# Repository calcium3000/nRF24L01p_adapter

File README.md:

# nRF24L01+ to Raspberry Pi adapter
Here lies a simple adapter for attaching one of those dirt-cheap nRF24L01+ modules to a Raspberry Pi (all models).  As seen on calcium3000.wordpress.com.

## Assembly
Pads are included for an optional 0805 surface mount capacitor, C1.  Some have reported that such a capacitor helps prevent wonkiness when transmitting at higher output (0dBm).  If extra capacitance at the power rails sounds peachy, install this guy first to make life easier later on.

Next, install P1 with a 2x4, 0.1" (2.54mm) female header such that the header sticks out of the side labeled *BOTTOM* -- this is also where the P1 designator sits.  P2 can either be another 2x4 female header for easy exchange of nRFs, or an nRF module can be soldered directly in.  Either way, make sure the header/radio protrudes from the opposite side of P1, labeled *TOP*.  If the nRF is directly soldered in, don't forget to clip the leads on the bottom side lest they sit dangerously close to the Broadcom chip and look quite ugly.

## Connection to RPi
This adapter is meant to plug directly into the GPIO header of a Raspberry Pi, facing inwards towards the processor.  Our adapter friend sits directly in the middle of the header on pins 17 to 24 (+3.3V to BCM 8) leaving 8 rows (16 pins) on each side when seated correctly.  See https://pinout.xyz for a good pin diagram.

Below is a table describing the pin functions and how they map from the RPi to the nRF24L01+.

| Pin function | nRF24L01+ | Raspberry Pi     |
| ------------ | --------- | ---------------- |
| VDD          | VDD (2)   | +3.3V (17)       |
| GND          | GND (1)   | GND (20)         |
| SCK          | SCK (5)   | BCM 11/SCK (23)  |
| MOSI         | MOSI (6)  | BCM 10/MOSI (19) |
| MISO         | MISO (7)  | BCM 9/MISO (21)  |
| CSN          | CSN (4)   | BCM 8/CE0 (24)   |
| CE           | CE (3)    | BCM 25 (22)      |
| IRQ          | IRQ (8)   | BCM 24 (18)      |

## License
Hardware files for this guy are licensed under the TAPR Open Hardware License.  See LICENSE.txt for more information.

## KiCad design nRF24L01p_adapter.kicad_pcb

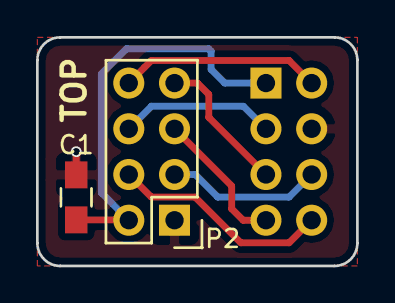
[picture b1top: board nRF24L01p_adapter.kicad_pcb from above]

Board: 2 copper layers, 17.8 x 12.7 mm, 3 parts (1 on the bottom side), 8 nets.

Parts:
C1: 10uF; C_0805_HandSoldering
P1: 2x4; Socket_Strip_Straight_2x04
P2: 2x4; Socket_Strip_Straight_2x04_mirrored

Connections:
CE: P1.6, P2.3
GND: C1.2, P1.4, P2.1
MISO: P1.5, P2.7
MOSI: P1.3, P2.6
SCK: P1.7, P2.5
VDD: C1.1, P1.1, P2.2
~CSN: P1.8, P2.4
~IRQ: P1.2, P2.8

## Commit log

2017-06-02 Updated README with pin connection section
